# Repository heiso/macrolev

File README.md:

<div align="center" >
  
  <br>
  <br>
  <br>
  <div>
    
  </div>
  <span>
    <a href="assets/keyboard-bot.png">bottom picture</a> - <a href="assets/pcb-bot.png">pcb picture</a> - 
  </span>
  <br>
  <br>
</div>

# Macrolev - Open Source Analog Keyboard

I use the two prototypes shown above as my daily drivers for both coding and gaming. They work well, and the current state of the web configurator is sufficient for seamlessly switching between coding and gaming modes. The current layout of my prototypes is Mac ISO azerty (FR).

## Disclaimer

This is still a work in progress. While the prototypes are functional, building one requires a good understanding of electronics and firmware development. If you're interested in creating your own, please be aware that you'll need experience with PCB assembly, microcontroller programming, and debugging embedded systems.

The Rev1 version shown in the images above requires an ST-Link programmer to flash the firmware, making setup more complex. Additionally, the keymap is _hardcoded_ in the firmware, so any changes to the key layout require recompiling and reflashing the firmware.

The second revision features a split PCB design consisting of a main board for the key layout and a separate breakout board. This two-board approach makes it easier to test and evaluate different microcontrollers. However, development is still in progress as the microcontroller board (currently planned to use an ESP32-S3) has not been finalized yet.

## Features

- **Analog Input:** Each key detects varying levels of pressure thanks to Hall Effect technology, allowing for a more responsive and sensitive typing experience.
- **Rapid Trigger Support:** Enables keys to actuate without fully releasing, allowing for faster response times during intense usage (e.g., gaming or rapid typing).
- **Continuous Rapid Trigger:** For keys that require repeated pressing (e.g., in gaming), this feature allows automatic repeated key input with a single press.
- **Tap and Hold Functionality:** Each key can be assigned two functions. A tap function for quick presses and a hold function for longer presses. This is ideal for combining shortcuts or creating multi-functional keys, such as assigning the right Shift key to act as an arrow up when tapped.
- **Web-Based Configurator:** Allows customization of key sensitivity and rapid trigger settings, with future updates planned to enable key mapping and expanded functionality. (see [screenshot](assets/web-configurator-screenshot.png))

## Todos

This is still a work in progress, the firt revision is working flawlessly but it is not that configurable yet. Here is some of the things I'm working on right now

- [x] PCB Rev 2.0
- [ ] Explore other MCUs
  - [ ] esp32-s3 (in progress)
  - [ ] nRF52840
  - [ ] RP2354 ?
- [ ] Add Bluetooth
- [ ] Configure layout and key mapping from the web interface
- [ ] Improve performances

## Links

- [keyboard layout](http://www.keyboard-layout-editor.com/#/gists/9dc992fd631d9f29cc5bdf738b10b4e4)
- [Onshape - Case](https://cad.onshape.com/documents/2af2025c576c4f084cb26625/w/9564bb1d9dfbd4b4af4294c8/e/e2406b8294380372b9116245)
- [Onshape - Low profile MX keycaps](https://cad.onshape.com/documents/93ff700fd3fbb6e9cde6f6e3)
- [Rev 1.0 Schema](https://kicanvas.org/?github=https%3A%2F%2Fgithub.com%2Fheiso%2Fmacrolev%2Fblob%2Fmain%2Fkicad%2FRev%25201.0%2Fmacrolev.kicad_sch)
- [Rev 1.0 Pcb](https://kicanvas.org/?github=https%3A%2F%2Fgithub.com%2Fheiso%2Fmacrolev%2Fblob%2Fmain%2Fkicad%2FRev%25201.0%2Fmacrolev.kicad_pcb)
- [Rev 2.0 Schema](https://kicanvas.org/?github=https%3A%2F%2Fgithub.com%2Fheiso%2Fmacrolev%2Fblob%2Fmain%2Fkicad%2FRev%25202.0%2Flayout_board%2Flayout_board.kicad_sch)
- [Rev 2.0 Pcb](https://kicanvas.org/?github=https%3A%2F%2Fgithub.com%2Fheiso%2Fmacrolev%2Fblob%2Fmain%2Fkicad%2FRev%25202.0%2Flayout_board%2Flayout_board.kicad_pcb)
- [Rev 2.0 Schema (daughter board)](https://kicanvas.org/?github=https%3A%2F%2Fgithub.com%2Fheiso%2Fmacrolev%2Fblob%2Fmain%2Fkicad%2FRev%25202.0%2Fdaughter_board%2Fdaughter_board.kicad_sch)
- [Rev 2.0 Pcb (daughter board)](https://kicanvas.org/?github=https%3A%2F%2Fgithub.com%2Fheiso%2Fmacrolev%2Fblob%2Fmain%2Fkicad%2FRev%25202.0%2Fdaughter_board%2Fdaughter_board.kicad_pcb)
- [Web Configurator](https://heiso.github.io/macrolev/)
- [Custom keycap set on Yuzu (azerty fr macos)](https://yuzukeycaps.com/c/2e35b096-fd41-4e16-bdcc-91adfbb08c2b)

## Misc

### References

- ~~[RP2040 Datasheet](https://datasheets.raspberrypi.com/rp2040/rp2040-datasheet.pdf)~~
- ~~[RP2040 Hardware Design](https://datasheets.raspberrypi.com/rp2040/hardware-design-with-rp2040.pdf)~~
- ~~[kb2040 doc](https://learn.adafruit.com/adafruit-kb2040/downloads)~~
- ~~[RPi Pico Debugger Shoe](https://github.com/ShawnHymel/rpi-pico-debugger-shoe)~~
- [Dilemma keyboard](https://github.com/Bastardkb/Dilemma)
- [0xB2 - splinky](https://github.com/plut0nium/0xB2)
- [Sub Reddit](https://www.reddit.com/r/PrintedCircuitBoard/search/?q=rp2040&restrict_sr=1&sr_nsfw=&include_over_18=1)
- [layout/design ref](https://geekhack.org/index.php?topic=103671.0)
- [cirque trackpad](https://www.cirque.com/glidepoint-circle-trackpads)
- [MagLev_Switch_MX](https://github.com/famichu/MagLev_Switch_MX)
- [Anatomy of a keyboard](https://matt3o.com/anatomy-of-a-keyboard/)
- [Switches/Stabs Kicad footprints from ebastler/marbastlib](https://github.com/ebastler/marbastlib)
- [Reddit Post about someone building a lekker switch based keyboard](https://www.reddit.com/r/PrintedCircuitBoard/comments/152kt63/review_request_analog_hall_effect_75_iso_keyboard/)
- [Riskable projects](https://github.com/riskable)
- [Fluxpad with lekker switches](https://github.com/sssata/fluxpad)
- [STM32F411CEU6 documentation](https://www.st.com/en/microcontrollers-microprocessors/stm32f411ce.html#documentation)
- [Wooting 60HE pcb](https://github.com/heiso/macrolev/tree/main/ref/Wooting-60HE)
- [Connecting to uncommon HID devices](https://developer.chrome.com/articles/hid)
- [HID Descriptor parser](https://eleccelerator.com/usbdescreqparser/)
- [peppapighs HE8 keyboard](https://github.com/peppapighs/HE8)
- [peppapighs libhmk library](https://github.com/peppapighs/libhmk)
- [nuphy configurator demo](https://drive.nuphy.io/?isDemoMode=true)
- [geonworks configurator demo](https://venom.how/)
- [wooting configurator demo](https://wootility.io/)

### Tooling

- [QMK keyboard test](https://config.qmk.fm/#/test)
- [Keyboard ghosting interactive demonstration](https://www.microsoft.com/applied-sciences/projects/anti-ghosting-demo)
- [Kicad lib marbastlib](https://github.com/ebastler/marbastlib)
- [Debug HardFault](https://interrupt.memfault.com/blog/cortex-m-hardfault-debug)
- [ai03 Plate Generator](https://kbplate.ai03.com/)
- [JLC2KiCad_lib](https://github.com/TousstNicolas/JLC2KiCad_lib)

Add footprints and symbols from jlcpcb with this cmd

```bash
JLC2KiCadLib <...LCSC refs> -dir JLCPCB -symbol_lib JLCPCB
```

### PCB reviews

- [Review request on PrintedCircuitBoard (Rev 1.0)](https://www.reddit.com/r/PrintedCircuitBoard/comments/17hjp88/review_request_analog_keyboard)
- [Second review request on PrintedCircuitBoard (Rev 1.0)](https://www.reddit.com/r/PrintedCircuitBoard/comments/17kqc2j/review_request_analog_keyboard_2/)
- [Third review request on PrintedCircuitBoard (Rev 2.0)](https://www.reddit.com/r/PrintedCircuitBoard/comments/1h432q5/review_request_open_source_analog_keyboard/)

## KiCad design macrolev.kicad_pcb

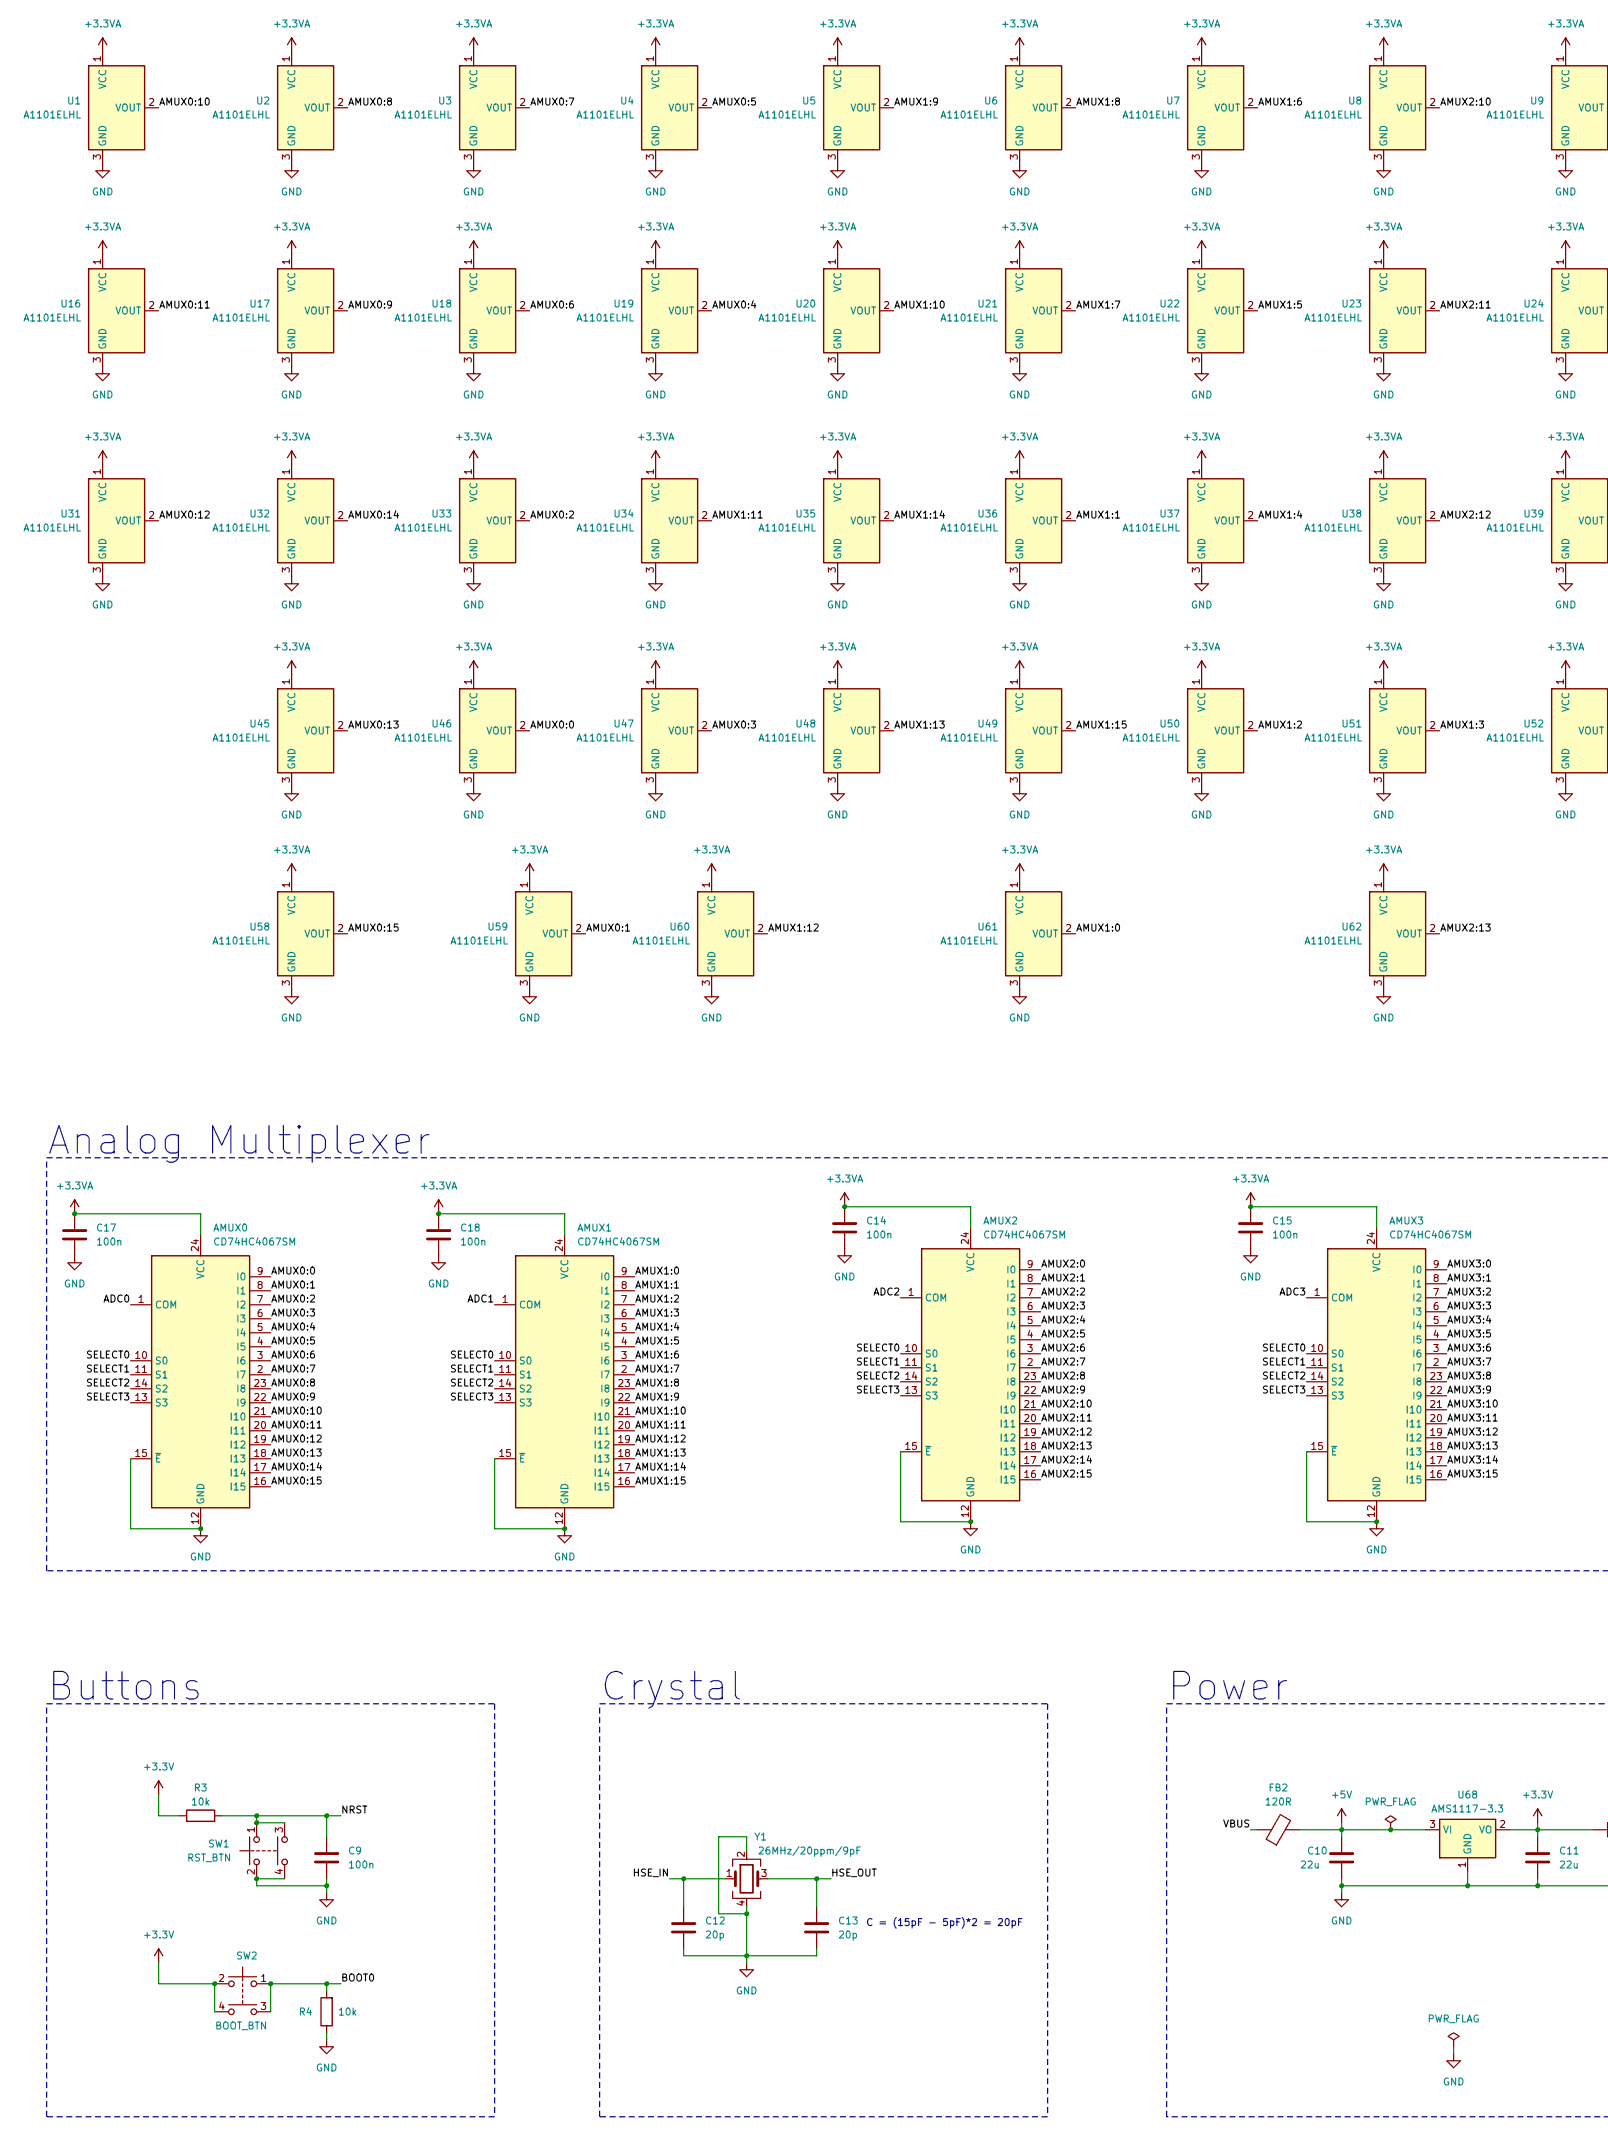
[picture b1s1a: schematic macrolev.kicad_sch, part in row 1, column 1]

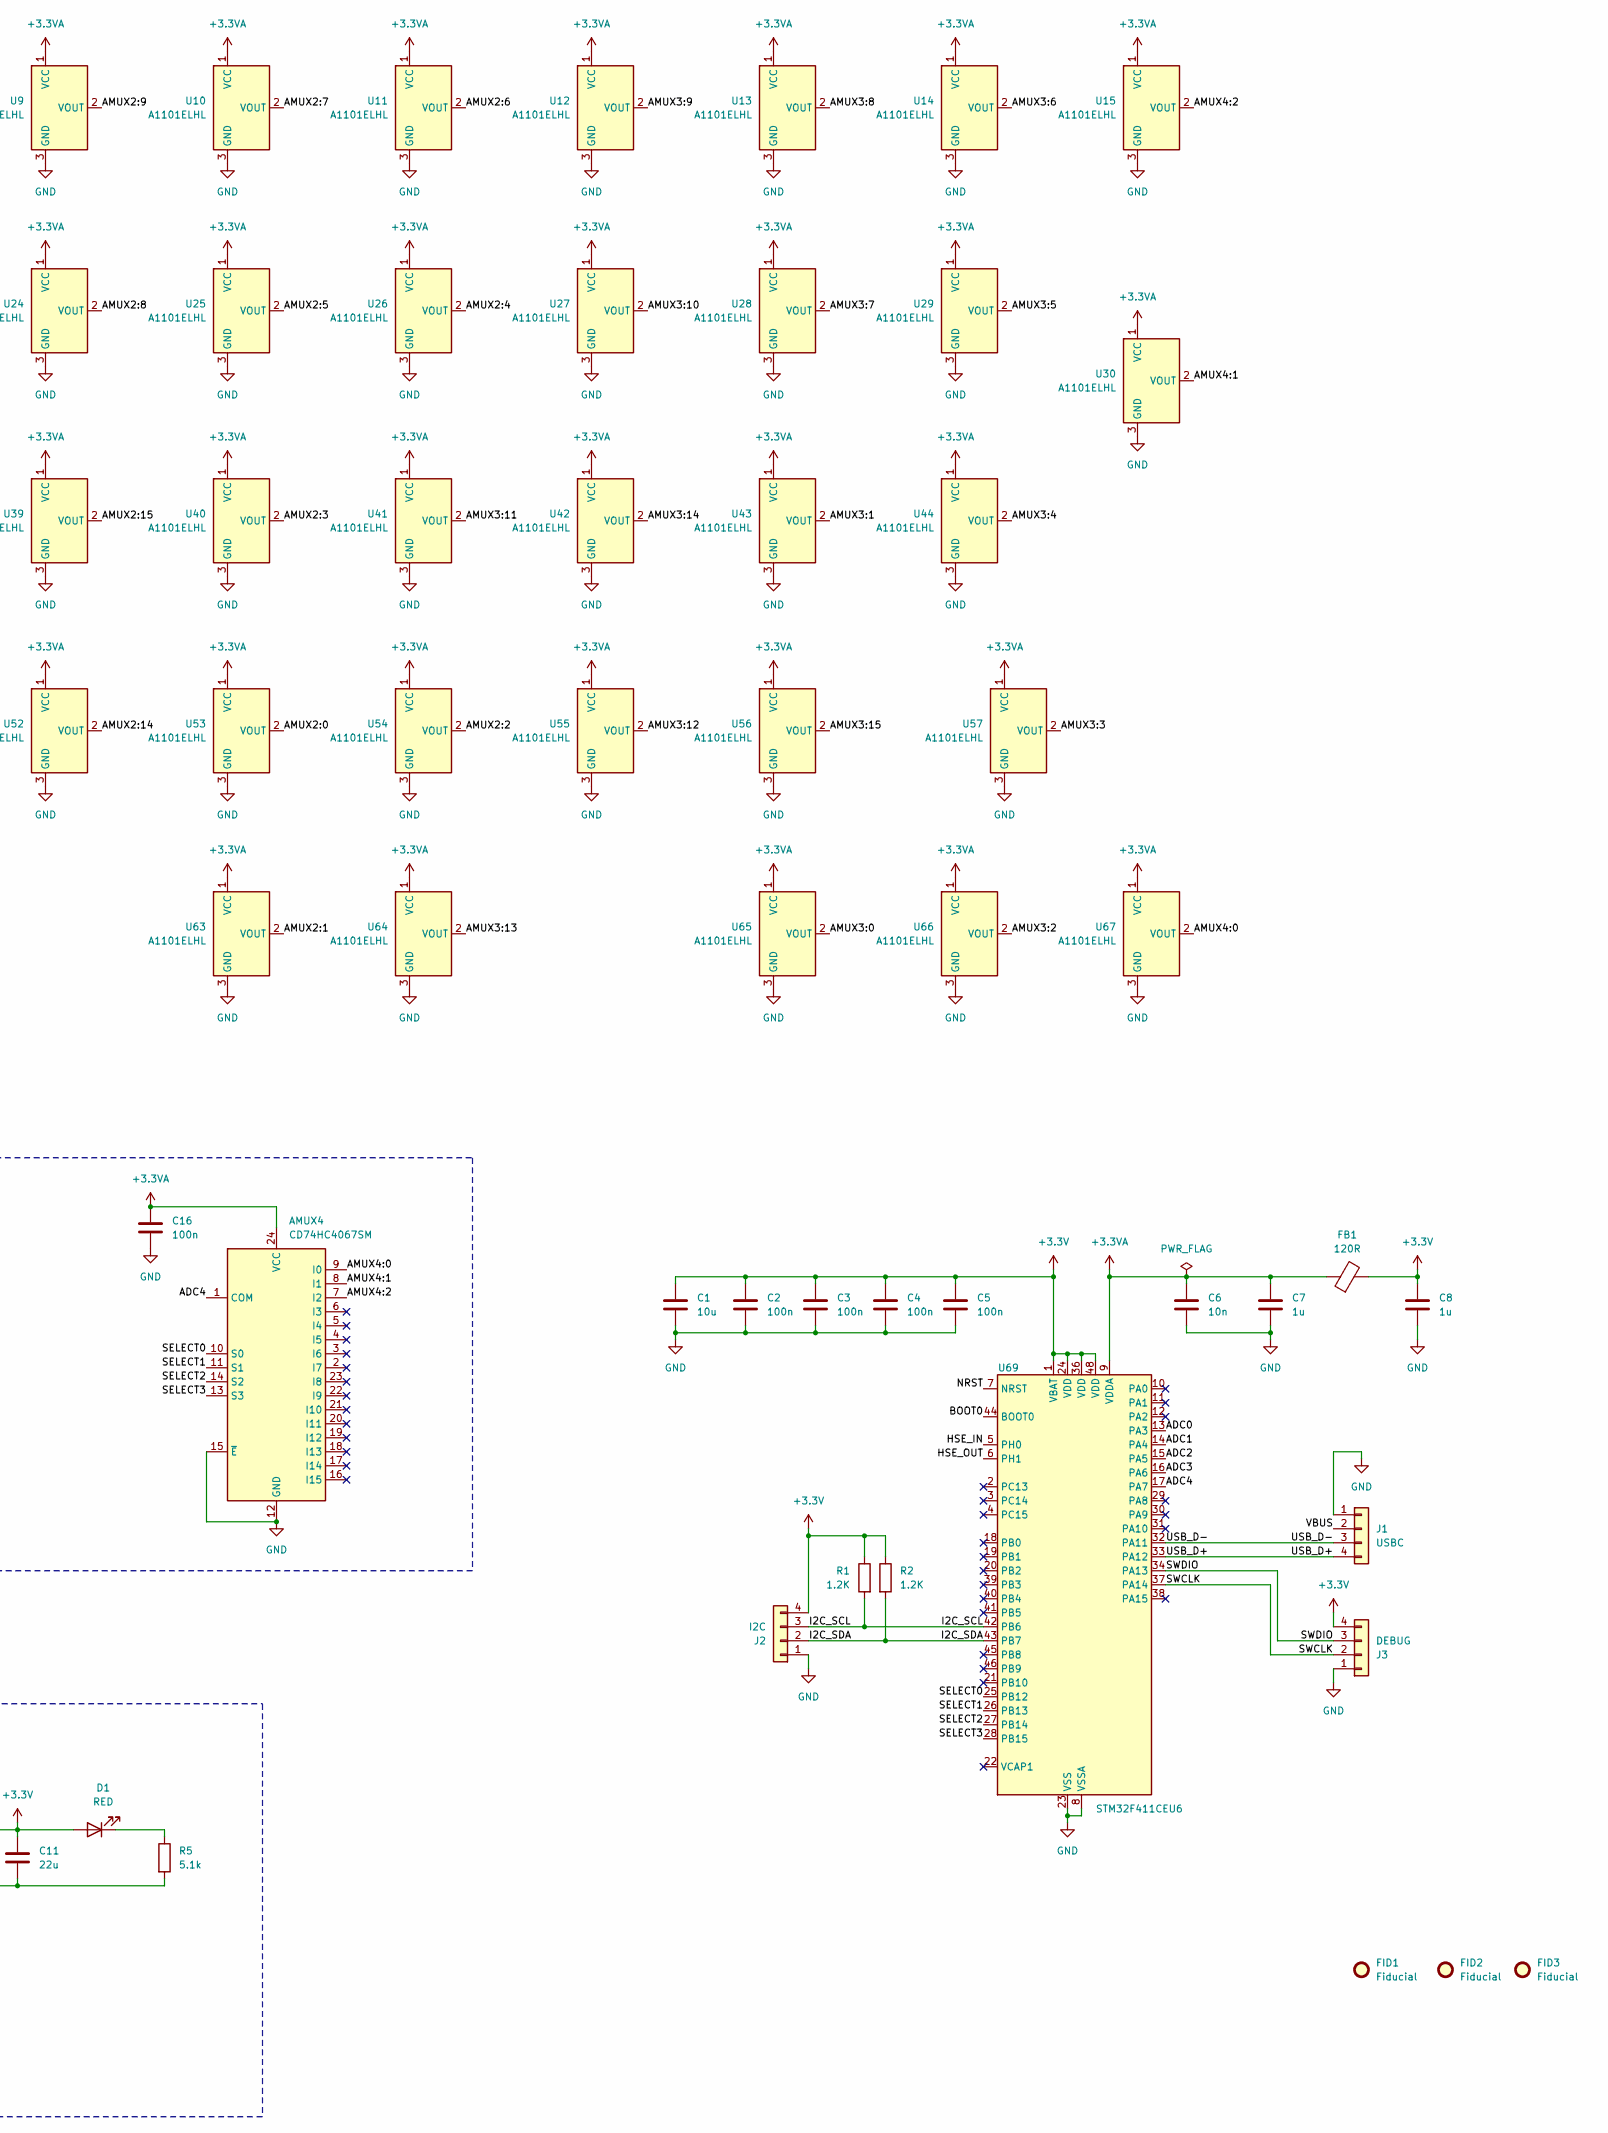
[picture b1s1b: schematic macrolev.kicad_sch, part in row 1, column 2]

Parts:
AMUX0, AMUX1, AMUX2, AMUX3, AMUX4: CD74HC4067SM; SSOP-24_5.3x8.2mm_P0.65mm; LCSC C179326
C1: 10u; C_0603_1608Metric_Pad1.08x0.95mm_HandSolder; LCSC C19702
C2, C3, C4, C5, C9, C14, C15, C16, C17, C18: 100n; C_0402_1005Metric_Pad0.74x0.62mm_HandSolder; LCSC C1525
C6: 10n; C_0402_1005Metric_Pad0.74x0.62mm_HandSolder; LCSC C15195
C7, C8: 1u; C_0402_1005Metric_Pad0.74x0.62mm_HandSolder; LCSC C52923
C10, C11: 22u; C_0805_2012Metric_Pad1.18x1.45mm_HandSolder; LCSC C45783
C12, C13: 20p; C_0402_1005Metric_Pad0.74x0.62mm_HandSolder; LCSC C1554
D1: RED; LED_0603_1608Metric_Pad1.05x0.95mm_HandSolder; LCSC C2286
FB1, FB2: 120R; L_0603_1608Metric_Pad1.05x0.95mm_HandSolder; LCSC C76892
FID1, FID2, FID3: Fiducial; Fiducial_1mm_Mask3mm
J1: USBC; PinHeader_1x04_P2.54mm_Vertical
J2: I2C; PinHeader_1x04_P2.54mm_Vertical
J3: DEBUG; PinHeader_1x04_P2.54mm_Vertical
R1, R2: 1.2K; R_0402_1005Metric_Pad0.72x0.64mm_HandSolder; LCSC C25862
R3, R4: 10k; R_0402_1005Metric_Pad0.72x0.64mm_HandSolder; LCSC C25744
R5: 5.1k; R_0402_1005Metric_Pad0.72x0.64mm_HandSolder; LCSC C25905
SW1: RST_BTN; SKRPACE010; LCSC C139797
SW2: BOOT_BTN; SKRPACE010; LCSC C139797
U1, U2, U3, U4, U5, U6, U7, U8, U9, U10, U11, U12, U13, U14, U15, U16, U17, U18, U19, U20, U21, U22, U23, U24, U25, U26, U27, U28, U29, U30, U31, U32, U33, U34, U35, U36, U37, U38, U39, U40, U41, U42, U43, U44, U45, U46, U47, U48, U49, U50, U51, U52, U53, U54, U55, U56, U57, U58, U59, U60, U61, U62, U63, U64, U65, U66, U67: A1101ELHL; SOT-23; LCSC C266230
U68: AMS1117-3.3; SOT-223-3_TabPin2; LCSC C6186
U69: STM32F411CEU6; QFN-48-1EP_7x7mm_P0.5mm_EP5.6x5.6mm; LCSC C60420
Y1: 26MHz/20ppm/9pF; Crystal_SMD_2520-4Pin_2.5x2.0mm; MPN 732-22526MF1Y-RX; LCSC C5371289

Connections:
+3.3V: C1.1, C2.1, C3.1, C4.1, C5.1, C8.1, C11.1, D1.2 (A), FB1.2, J2.4, J3.4, R1.1, R2.1, R3.1, SW2.2, SW2.4, U68.2 (VO), U69.1 (VBAT), U69.24 (VDD), U69.36 (VDD), U69.48 (VDD)
+3.3VA: AMUX0.24 (VCC), AMUX1.24 (VCC), AMUX2.24 (VCC), AMUX3.24 (VCC), AMUX4.24 (VCC), C6.1, C7.1, C14.1, C15.1, C16.1, C17.1, C18.1, FB1.1, U1.1 (VCC), U2.1 (VCC), U3.1 (VCC), U4.1 (VCC), U5.1 (VCC), U6.1 (VCC), U7.1 (VCC), U8.1 (VCC), U9.1 (VCC), U10.1 (VCC), U11.1 (VCC), U12.1 (VCC), U13.1 (VCC), U14.1 (VCC), U15.1 (VCC), U16.1 (VCC), U17.1 (VCC), U18.1 (VCC), U19.1 (VCC), U20.1 (VCC), U21.1 (VCC), U22.1 (VCC), U23.1 (VCC), U24.1 (VCC), U25.1 (VCC), U26.1 (VCC), U27.1 (VCC), U28.1 (VCC), U29.1 (VCC), U30.1 (VCC), U31.1 (VCC), U32.1 (VCC), U33.1 (VCC), U34.1 (VCC), U35.1 (VCC), U36.1 (VCC), U37.1 (VCC), U38.1 (VCC), U39.1 (VCC), U40.1 (VCC), U41.1 (VCC), U42.1 (VCC), U43.1 (VCC), U44.1 (VCC), U45.1 (VCC), U46.1 (VCC), U47.1 (VCC), U48.1 (VCC), U49.1 (VCC), U50.1 (VCC), U51.1 (VCC), U52.1 (VCC), U53.1 (VCC), U54.1 (VCC), U55.1 (VCC), U56.1 (VCC), U57.1 (VCC), U58.1 (VCC), U59.1 (VCC), U60.1 (VCC), U61.1 (VCC), U62.1 (VCC), U63.1 (VCC), U64.1 (VCC), U65.1 (VCC), U66.1 (VCC), U67.1 (VCC), U69.9 (VDDA)
+5V: C10.1, FB2.2, U68.3 (VI)
/ADC0: AMUX0.1 (COM), U69.13 (PA3)
/ADC1: AMUX1.1 (COM), U69.14 (PA4)
/ADC2: AMUX2.1 (COM), U69.15 (PA5)
/ADC3: AMUX3.1 (COM), U69.16 (PA6)
/ADC4: AMUX4.1 (COM), U69.17 (PA7)
/AMUX0:0: AMUX0.9 (I0), U46.2 (VOUT)
/AMUX0:1: AMUX0.8 (I1), U59.2 (VOUT)
/AMUX0:2: AMUX0.7 (I2), U33.2 (VOUT)
/AMUX0:3: AMUX0.6 (I3), U47.2 (VOUT)
/AMUX0:4: AMUX0.5 (I4), U19.2 (VOUT)
/AMUX0:5: AMUX0.4 (I5), U4.2 (VOUT)
/AMUX0:6: AMUX0.3 (I6), U18.2 (VOUT)
/AMUX0:7: AMUX0.2 (I7), U3.2 (VOUT)
/AMUX0:8: AMUX0.23 (I8), U2.2 (VOUT)
/AMUX0:9: AMUX0.22 (I9), U17.2 (VOUT)
/AMUX0:10: AMUX0.21 (I10), U1.2 (VOUT)
/AMUX0:11: AMUX0.20 (I11), U16.2 (VOUT)
/AMUX0:12: AMUX0.19 (I12), U31.2 (VOUT)
/AMUX0:13: AMUX0.18 (I13), U45.2 (VOUT)
/AMUX0:14: AMUX0.17 (I14), U32.2 (VOUT)
/AMUX0:15: AMUX0.16 (I15), U58.2 (VOUT)
/AMUX1:0: AMUX1.9 (I0), U61.2 (VOUT)
/AMUX1:1: AMUX1.8 (I1), U36.2 (VOUT)
/AMUX1:2: AMUX1.7 (I2), U50.2 (VOUT)
/AMUX1:3: AMUX1.6 (I3), U51.2 (VOUT)
/AMUX1:4: AMUX1.5 (I4), U37.2 (VOUT)
/AMUX1:5: AMUX1.4 (I5), U22.2 (VOUT)
/AMUX1:6: AMUX1.3 (I6), U7.2 (VOUT)
/AMUX1:7: AMUX1.2 (I7), U21.2 (VOUT)
/AMUX1:8: AMUX1.23 (I8), U6.2 (VOUT)
/AMUX1:9: AMUX1.22 (I9), U5.2 (VOUT)
/AMUX1:10: AMUX1.21 (I10), U20.2 (VOUT)
/AMUX1:11: AMUX1.20 (I11), U34.2 (VOUT)
/AMUX1:12: AMUX1.19 (I12), U60.2 (VOUT)
/AMUX1:13: AMUX1.18 (I13), U48.2 (VOUT)
/AMUX1:14: AMUX1.17 (I14), U35.2 (VOUT)
/AMUX1:15: AMUX1.16 (I15), U49.2 (VOUT)
/AMUX2:0: AMUX2.9 (I0), U53.2 (VOUT)
/AMUX2:1: AMUX2.8 (I1), U63.2 (VOUT)
/AMUX2:2: AMUX2.7 (I2), U54.2 (VOUT)
/AMUX2:3: AMUX2.6 (I3), U40.2 (VOUT)
/AMUX2:4: AMUX2.5 (I4), U26.2 (VOUT)
/AMUX2:5: AMUX2.4 (I5), U25.2 (VOUT)
/AMUX2:6: AMUX2.3 (I6), U11.2 (VOUT)
/AMUX2:7: AMUX2.2 (I7), U10.2 (VOUT)
/AMUX2:8: AMUX2.23 (I8), U24.2 (VOUT)
/AMUX2:9: AMUX2.22 (I9), U9.2 (VOUT)
/AMUX2:10: AMUX2.21 (I10), U8.2 (VOUT)
/AMUX2:11: AMUX2.20 (I11), U23.2 (VOUT)
/AMUX2:12: AMUX2.19 (I12), U38.2 (VOUT)
/AMUX2:13: AMUX2.18 (I13), U62.2 (VOUT)
/AMUX2:14: AMUX2.17 (I14), U52.2 (VOUT)
/AMUX2:15: AMUX2.16 (I15), U39.2 (VOUT)
/AMUX3:0: AMUX3.9 (I0), U65.2 (VOUT)
/AMUX3:1: AMUX3.8 (I1), U43.2 (VOUT)
/AMUX3:2: AMUX3.7 (I2), U66.2 (VOUT)
/AMUX3:3: AMUX3.6 (I3), U57.2 (VOUT)
/AMUX3:4: AMUX3.5 (I4), U44.2 (VOUT)
/AMUX3:5: AMUX3.4 (I5), U29.2 (VOUT)
/AMUX3:6: AMUX3.3 (I6), U14.2 (VOUT)
/AMUX3:7: AMUX3.2 (I7), U28.2 (VOUT)
/AMUX3:8: AMUX3.23 (I8), U13.2 (VOUT)
/AMUX3:9: AMUX3.22 (I9), U12.2 (VOUT)
/AMUX3:10: AMUX3.21 (I10), U27.2 (VOUT)
/AMUX3:11: AMUX3.20 (I11), U41.2 (VOUT)
/AMUX3:12: AMUX3.19 (I12), U55.2 (VOUT)
/AMUX3:13: AMUX3.18 (I13), U64.2 (VOUT)
/AMUX3:14: AMUX3.17 (I14), U42.2 (VOUT)
/AMUX3:15: AMUX3.16 (I15), U56.2 (VOUT)
/AMUX4:0: AMUX4.9 (I0), U67.2 (VOUT)
/AMUX4:1: AMUX4.8 (I1), U30.2 (VOUT)
/AMUX4:2: AMUX4.7 (I2), U15.2 (VOUT)
/BOOT0: R4.2, SW2.1, SW2.3, U69.44 (BOOT0)
/HSE_IN: C12.1, U69.5 (PH0), Y1.1
/HSE_OUT: C13.1, U69.6 (PH1), Y1.3
/I2C_SCL: J2.3, R1.2, U69.42 (PB6)
/I2C_SDA: J2.2, R2.2, U69.43 (PB7)
/NRST: C9.1, R3.2, SW1.1, SW1.3, U69.7 (NRST)
/SELECT0: AMUX0.10 (S0), AMUX1.10 (S0), AMUX2.10 (S0), AMUX3.10 (S0), AMUX4.10 (S0), U69.25 (PB12)
/SELECT1: AMUX0.11 (S1), AMUX1.11 (S1), AMUX2.11 (S1), AMUX3.11 (S1), AMUX4.11 (S1), U69.26 (PB13)
/SELECT2: AMUX0.14 (S2), AMUX1.14 (S2), AMUX2.14 (S2), AMUX3.14 (S2), AMUX4.14 (S2), U69.27 (PB14)
/SELECT3: AMUX0.13 (S3), AMUX1.13 (S3), AMUX2.13 (S3), AMUX3.13 (S3), AMUX4.13 (S3), U69.28 (PB15)
/SWCLK: J3.2, U69.37 (PA14)
/SWDIO: J3.3, U69.34 (PA13)
/USB_D+: J1.4, U69.33 (PA12)
/USB_D-: J1.3, U69.32 (PA11)
/VBUS: FB2.1, J1.2
GND: AMUX0.12 (GND), AMUX0.15 (~E), AMUX1.12 (GND), AMUX1.15 (~E), AMUX2.12 (GND), AMUX2.15 (~E), AMUX3.12 (GND), AMUX3.15 (~E), AMUX4.12 (GND), AMUX4.15 (~E), C1.2, C2.2, C3.2, C4.2, C5.2, C6.2, C7.2, C8.2, C9.2, C10.2, C11.2, C12.2, C13.2, C14.2, C15.2, C16.2, C17.2, C18.2, J1.1, J2.1, J3.1, R4.1, R5.2, SW1.2, SW1.4, U1.3 (GND), U2.3 (GND), U3.3 (GND), U4.3 (GND), U5.3 (GND), U6.3 (GND), U7.3 (GND), U8.3 (GND), U9.3 (GND), U10.3 (GND), U11.3 (GND), U12.3 (GND), U13.3 (GND), U14.3 (GND), U15.3 (GND), U16.3 (GND), U17.3 (GND), U18.3 (GND), U19.3 (GND), U20.3 (GND), U21.3 (GND), U22.3 (GND), U23.3 (GND), U24.3 (GND), U25.3 (GND), U26.3 (GND), U27.3 (GND), U28.3 (GND), U29.3 (GND), U30.3 (GND), U31.3 (GND), U32.3 (GND), U33.3 (GND), U34.3 (GND), U35.3 (GND), U36.3 (GND), U37.3 (GND), U38.3 (GND), U39.3 (GND), U40.3 (GND), U41.3 (GND), U42.3 (GND), U43.3 (GND), U44.3 (GND), U45.3 (GND), U46.3 (GND), U47.3 (GND), U48.3 (GND), U49.3 (GND), U50.3 (GND), U51.3 (GND), U52.3 (GND), U53.3 (GND), U54.3 (GND), U55.3 (GND), U56.3 (GND), U57.3 (GND), U58.3 (GND), U59.3 (GND), U60.3 (GND), U61.3 (GND), U62.3 (GND), U63.3 (GND), U64.3 (GND), U65.3 (GND), U66.3 (GND), U67.3 (GND), U68.1 (GND), U69.8 (VSSA), U69.23 (VSS), U69.35 (VSS), U69.47 (VSS), U69.49 (VSS), Y1.2, Y1.4
unnamed: D1.1 (K), R5.1

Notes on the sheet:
Power
Buttons
C = (15pF - 5pF)*2 = 20pF
Crystal
Analog Multiplexer

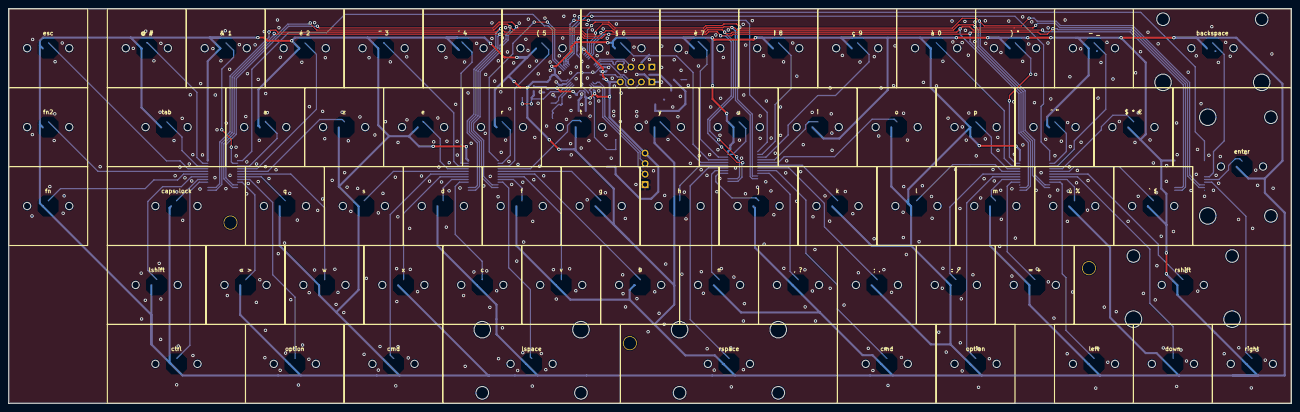
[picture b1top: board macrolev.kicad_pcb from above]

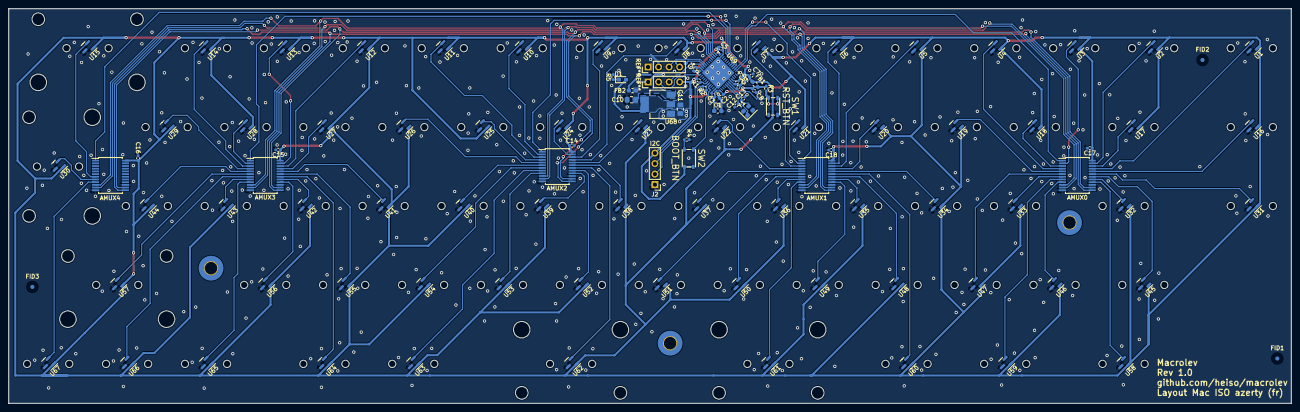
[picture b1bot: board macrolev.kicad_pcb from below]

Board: 2 copper layers, 309.6 x 95.2 mm, 174 parts (107 on the bottom side), 87 nets.

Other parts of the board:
! 8: SW_MX_Lekker_1u
" 3: SW_MX_Lekker_1u
$ * €: SW_MX_Lekker_1u
& 1: SW_MX_Lekker_1u
' 4: SW_MX_Lekker_1u
( 5: SW_MX_Lekker_1u
) °: SW_MX_Lekker_1u
, ?: SW_MX_Lekker_1u
- _: SW_MX_Lekker_1u
: /: SW_MX_Lekker_1u
; .: SW_MX_Lekker_1u
< >: SW_MX_Lekker_1u
= +: SW_MX_Lekker_1u
@ #: SW_MX_Lekker_1u
^ ¨: SW_MX_Lekker_1u
` £: SW_MX_Lekker_1u
a: SW_MX_Lekker_1u
b: SW_MX_Lekker_1u
backspace: SW_MX_Lekker
c: SW_MX_Lekker_1u
caps lock: SW_MX_Lekker_1.75u
cmd: SW_MX_Lekker_1.25u
cmd#2: SW_MX_Lekker_1.25u
ctrl: SW_MX_Lekker_1.75u
d: SW_MX_Lekker_1u
down: SW_MX_Lekker_1u
e: SW_MX_Lekker_1u
enter: SW_MX_Lekker
esc: SW_MX_Lekker_1u
f: SW_MX_Lekker_1u
fn, fn2: SW_MX_Lekker_1u
g: SW_MX_Lekker_1u
h: SW_MX_Lekker_1u
i: SW_MX_Lekker_1u
j: SW_MX_Lekker_1u
k: SW_MX_Lekker_1u
l: SW_MX_Lekker_1u
left: SW_MX_Lekker_1u
lshift: SW_MX_Lekker_1.25u
lspace: SW_MX_Lekker
m: SW_MX_Lekker_1u
n: SW_MX_Lekker_1u
o: SW_MX_Lekker_1u
option: SW_MX_Lekker_1.25u
option#2: SW_MX_Lekker_1u
p: SW_MX_Lekker_1u
q: SW_MX_Lekker_1u
r: SW_MX_Lekker_1u
right: SW_MX_Lekker_1u
rshift: SW_MX_Lekker
rspace: SW_MX_Lekker
s: SW_MX_Lekker_1u
t: SW_MX_Lekker_1u
tab: SW_MX_Lekker_1.5u
u: SW_MX_Lekker_1u
v: SW_MX_Lekker_1u
w: SW_MX_Lekker_1u
x: SW_MX_Lekker_1u
y: SW_MX_Lekker_1u
z: SW_MX_Lekker_1u
§ 6: SW_MX_Lekker_1u
à 0: SW_MX_Lekker_1u
ç 9: SW_MX_Lekker_1u
è 7: SW_MX_Lekker_1u
é 2: SW_MX_Lekker_1u
ù %: SW_MX_Lekker_1u

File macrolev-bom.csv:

"Item","Qty","Reference(s)","Value","LibPart","Footprint","Datasheet","DNP","LCSC"
"1","5","AMUX0, AMUX1, AMUX2, AMUX3, AMUX4","CD74HC4067SM","74xx:CD74HC4067SM","Package_SO:SSOP-24_5.3x8.2mm_P0.65mm","http://www.ti.com/lit/ds/symlink/cd74hc4067.pdf","","C98457"
"2","1","C1","10u","Device:C","Capacitor_SMD:C_0603_1608Metric_Pad1.08x0.95mm_HandSolder","~","","C19702"
"3","10","C2, C3, C4, C5, C9, C14, C15, C16, C17, C18","100n","Device:C","Capacitor_SMD:C_0402_1005Metric_Pad0.74x0.62mm_HandSolder","~","","C1525"
"4","1","C6","10n","Device:C","Capacitor_SMD:C_0402_1005Metric_Pad0.74x0.62mm_HandSolder","~","","C15195"
"5","2","C7, C8","1u","Device:C","Capacitor_SMD:C_0402_1005Metric_Pad0.74x0.62mm_HandSolder","~","","C52923"
"6","2","C10, C11","22u","Device:C","Capacitor_SMD:C_0805_2012Metric_Pad1.18x1.45mm_HandSolder","~","","C45783"
"7","2","C12, C13","20p","Device:C","Capacitor_SMD:C_0402_1005Metric_Pad0.74x0.62mm_HandSolder","~","","C1554"
"8","1","D1","RED","Device:LED","LED_SMD:LED_0603_1608Metric_Pad1.05x0.95mm_HandSolder","~","","C2286"
"9","2","FB1, FB2","120R","Device:FerriteBead","Inductor_SMD:L_0603_1608Metric_Pad1.05x0.95mm_HandSolder","~","","C76892"
"14","2","R1, R2","1.2K","Device:R","Resistor_SMD:R_0402_1005Metric_Pad0.72x0.64mm_HandSolder","~","","C25862"
"15","2","R3, R4","10k","Device:R","Resistor_SMD:R_0402_1005Metric_Pad0.72x0.64mm_HandSolder","~","","C25744"
"16","1","R5","5.1k","Device:R","Resistor_SMD:R_0402_1005Metric_Pad0.72x0.64mm_HandSolder","~","","C25905"
"17","1","SW1","RST_BTN","Switch:SW_Push_Dual","switch:SKRPACE010","~","","C139797"
"18","1","SW2","BOOT_BTN","Switch:SW_Push_Dual","switch:SKRPACE010","~","","C139797"
"19","67","U1, U2, U3, U4, U5, U6, U7, U8, U9, U10, U11, U12, U13, U14, U15, U16, U17, U18, U19, U20, U21, U22, U23, U24, U25, U26, U27, U28, U29, U30, U31, U32, U33, U34, U35, U36, U37, U38, U39, U40, U41, U42, U43, U44, U45, U46, U47, U48, U49, U50, U51, U52, U53, U54, U55, U56, U57, U58, U59, U60, U61, U62, U63, U64, U65, U66, U67","A1101ELHL","Sensor_Magnetic:A1101ELHL","Package_TO_SOT_SMD:SOT-23","https://www.allegromicro.com/-/media/files/datasheets/a110x-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","","C266230"
"20","1","U68","AMS1117-3.3","Regulator_Linear:AMS1117-3.3","Package_TO_SOT_SMD:SOT-223-3_TabPin2","http://www.advanced-monolithic.com/pdf/ds1117.pdf","","C6186"
"21","1","U69","STM32F411CEU6","MCU_ST_STM32F4:STM32F411CEUx","Package_DFN_QFN:QFN-48-1EP_7x7mm_P0.5mm_EP5.6x5.6mm","https://www.st.com/resource/en/datasheet/stm32f411ce.pdf","","C60420"
"22","1","Y1","26MHz/20ppm/9pF","Device:Crystal_GND24","Crystal:Crystal_SMD_2520-4Pin_2.5x2.0mm","~","","C5371289"
